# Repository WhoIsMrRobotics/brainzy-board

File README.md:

# Brainzy Board

Il s'agit d'une alternative aux cartes Arduino pour facilement construire son propre robot différentiel ou omnidirectionel. Basé sur une [Teensy 3.5](https://www.pjrc.com/store/teensy35.html), la Brainzy board se programme en C++ à travers l'[IDE Arduino](https://www.arduino.cc/en/Main/Software) à l'aide de la [bibliothèque Brainzy](https://github.com/WhoIsMrRobotics/brainzy-library). De nombreux modules peuvent être ajoutés à la carte pour étendre la complexité de vos créations.

Il existe deux types de modules :
* Les *Widgets*, dont la connection se fait par des connecteurs magnétiques et la communication via un bus I2C ;
* Les *extensions*, dont la connection se fait par des connecteurs standards et la communication via des bus SPI, UART, et/ou I2C.

Pour plus d'information, consultez notre site [www.mr-robotics.com](https://www.mr-robotics.com/).

**Caractéristiques de la Brainzy Board**

* *Mode d'utilisation :* 2 choix possibles pour le déplacement du robot : entrainement différenciel (2 roues) ou entrainement omnidirectionel (3 roues)
* *Dimensions de la carte :* 100mm x 100mm (forme hexagonale)
* *Moyens de communication :* USB, Bluetooth et Wifi

**Ports Entrées/Sorties**

* 1 port micro-USB
* 8 ports I2C, 3 ports SPI, 2 ports UART
* 3 ports pour des moteurs DC dotés de codeurs incrémentaux (deux channels)
* 1 lecteur de carte nano-SD
* 1 port pour vérifier l'état de charge de la batterie (jusqu'à 3 cellules)
* 1 Buzzer
* 1 interrupteur programmable
* 2 LEDs programmables

**Modules intégrés**

* 1 Module bluetooth (HC-05)
* 1 Module Wifi (ESP8266-01)

**Exemples de Widgets associés**

* IMU : accéléromètre 3 axes + gyroscope 3 axes (MPU-6050)
* Système d'éclairage : NeoPixels (WS2812B)
* Télémètre à ultrasons : Sonar (HC-SR04)
* Télémètre infrarouge : Sharp (GP2Y0A41SK0F)
* ...

**Exemples d'extensions associées**

* Bras poly-articulé
* Système de webcam pilotée
* Télécomande bluetooth
* Écran tactile
* ...

## Comment l'obtenir ?

Vous pouvez la commander en [nous contactant](mailto:bonjour@mr-robotics.com) ou suivre les étapes suivantes :
1. Réalisez le PCB à l'aide des fichiers GERBER.
2. Commandez les composants répertoriés dans le fichier BOM, puis soudez les.
3. Soudez une Teensy 3.5 en faisant attention aux indications suivantes.

## Quelques tutoriels

* Pour obtenir un modèle CAO de la carte, consultez [ce lien](https://www.youtube.com/watch?v=ekHAkWB-WTM).
* Pour générer les fichiers Gerber nécessaire à la production du PCB, consultez [ce lien](https://learn.sparkfun.com/tutorials/designing-pcbs-advanced-smd/gerber-generation).

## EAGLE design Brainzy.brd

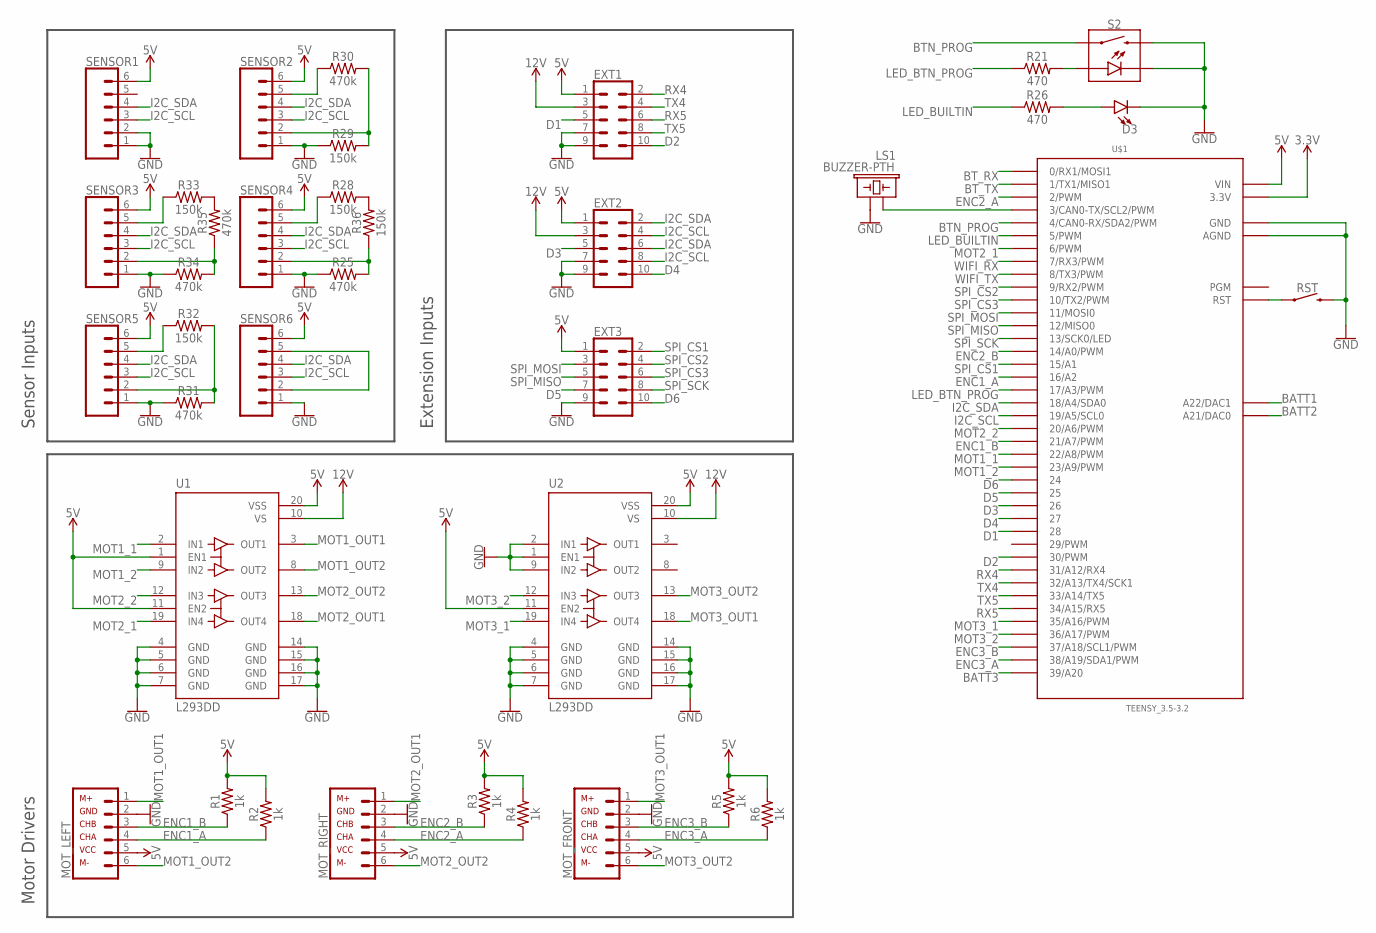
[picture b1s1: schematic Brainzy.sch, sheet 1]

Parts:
D3: LED-FKIT-1206; FKIT-LED-1206
EXT1, EXT2, EXT3: CONN_05X2SHD_LOCK; 2X5-SHROUDED_LOCK
LS1: BUZZER-PTH; BUZZER-12MM
MOT_FRONT: DC-MOTOR-CONNECTOR; JST-PH6
MOT_LEFT: DC-MOTOR-CONNECTOR; JST-PH6
MOT_RIGHT: DC-MOTOR-CONNECTOR; JST-PH6
R1, R2, R3, R4, R5, R6: 1k; 1206
R21, R26: 470; 1206
R25, R30, R31, R34, R35: 470k; 1206
R28, R29, R32, R33, R36: 150k; 1206
RST: MOMENTARY-SWITCH-SPST-PTH-6.0MM; TACTILE_SWITCH_PTH_6.0MM
S2: MOMENTARY-SWITCH-SPST-LED-PTH-12MM; TACTILE_SWITCH_LED_PTH_12MM
SENSOR1, SENSOR2, SENSOR3, SENSOR4, SENSOR5, SENSOR6: JST-ZH6
U1, U2: L293DD; SOIC127P1033X265-20N
U$1: TEENSY_3.5-3.2

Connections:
3.3V: U$1.3.3V, U$1.3.3V1 (3.3V), U$1.3.3V2 (3.3V), U$1.3.3V3 (3.3V); also elsewhere on the board
5V: EXT1.1, EXT2.1, EXT3.1, MOT_FRONT.5 (5-CHA), MOT_LEFT.5 (5-CHA), MOT_RIGHT.5 (5-CHA), R1.2, R2.2, R3.2, R4.2, R5.2, R6.2, SENSOR1.6, SENSOR2.6, SENSOR3.6, SENSOR4.6, SENSOR5.6, SENSOR6.6, U1.1 (EN1), U1.11 (EN2), U1.20 (VSS), U2.11 (EN2), U2.20 (VSS), U$1.VIN; also elsewhere on the board
12V: EXT1.3, EXT2.3, U1.10 (VS), U2.10 (VS); also elsewhere on the board
BATT1: U$1.A22 (A22/DAC1); also elsewhere on the board
BATT2: U$1.A21 (A21/DAC0); also elsewhere on the board
BATT3: U$1.39/A20; also elsewhere on the board
BTN_PROG: S2.4 (1), U$1.4 (4/CAN0-RX/SDA2/PWM)
BT_RX: U$1.0 (0/RX1/MOSI1); also elsewhere on the board
BT_TX: U$1.1 (1/TX1/MISO1); also elsewhere on the board
BUZZER: LS1.+ (1), U$1.3 (3/CAN0-TX/SCL2/PWM)
D1: EXT1.5, U$1.28
D2: EXT1.10, U$1.30 (30/PWM)
D3: EXT2.5, U$1.26
D4: EXT2.10, U$1.27
D5: EXT3.7, U$1.25
D6: EXT3.10, U$1.24
ENC1_A: MOT_LEFT.4 (4-GND), R2.1, U$1.16/A2
ENC1_B: MOT_LEFT.3 (3-VCC), R1.1, U$1.21/A7 (21/A7/PWM)
ENC2_A: MOT_RIGHT.4 (4-GND), R4.1, U$1.2 (2/PWM)
ENC2_B: MOT_RIGHT.3 (3-VCC), R3.1, U$1.14/A0 (14/A0/PWM)
ENC3_A: MOT_FRONT.4 (4-GND), R6.1, U$1.38/A19 (38/A19/SDA1/PWM)
ENC3_B: MOT_FRONT.3 (3-VCC), R5.1, U$1.37/A18 (37/A18/SCL1/PWM)
GND: D3.C, EXT1.7, EXT1.9, EXT2.7, EXT2.9, EXT3.9, LS1.- (2), MOT_FRONT.2 (2-M+), MOT_LEFT.2 (2-M+), MOT_RIGHT.2 (2-M+), R25.1, R29.1, R31.1, R34.1, RST.3 (2), S2.2, S2.C, SENSOR1.1, SENSOR1.2, SENSOR2.1, SENSOR3.1, SENSOR4.1, SENSOR5.1, SENSOR6.1, U1.4 (GND), U1.5 (GND), U1.6 (GND), U1.7 (GND), U1.14 (GND), U1.15 (GND), U1.16 (GND), U1.17 (GND), U2.1 (EN1), U2.2 (IN1), U2.4 (GND), U2.5 (GND), U2.6 (GND), U2.7 (GND), U2.9 (IN2), U2.14 (GND), U2.15 (GND), U2.16 (GND), U2.17 (GND), U$1.AGND, U$1.GND, U$1.GND1 (GND), U$1.GND2 (GND), U$1.GND3 (GND); also elsewhere on the board
I2C_SCL: EXT2.4, EXT2.8, SENSOR1.3, SENSOR2.3, SENSOR3.3, SENSOR4.3, SENSOR5.3, SENSOR6.3, U$1.19/A5 (19/A5/SCL0)
I2C_SDA: EXT2.2, EXT2.6, SENSOR1.4, SENSOR2.4, SENSOR3.4, SENSOR4.4, SENSOR5.4, SENSOR6.4, U$1.18/A4 (18/A4/SDA0)
LED_BTN_PROG: R21.1, U$1.17/A3 (17/A3/PWM)
LED_BUILTIN: R26.1, U$1.5 (5/PWM)
MOT1_1: U1.2 (IN1), U$1.22/A8 (22/A8/PWM)
MOT1_2: U1.9 (IN2), U$1.23/A9 (23/A9/PWM)
MOT1_OUT1: MOT_LEFT.1 (1-M-), U1.3 (OUT1)
MOT1_OUT2: MOT_LEFT.6 (6-CHB), U1.8 (OUT2)
MOT2_1: U1.19 (IN4), U$1.6 (6/PWM)
MOT2_2: U1.12 (IN3), U$1.20/A6 (20/A6/PWM)
MOT2_OUT1: MOT_RIGHT.1 (1-M-), U1.18 (OUT4)
MOT2_OUT2: MOT_RIGHT.6 (6-CHB), U1.13 (OUT3)
MOT3_1: U2.19 (IN4), U$1.35/A16 (35/A16/PWM)
MOT3_2: U2.12 (IN3), U$1.36/A17 (36/A17/PWM)
MOT3_OUT1: MOT_FRONT.1 (1-M-), U2.18 (OUT4)
MOT3_OUT2: MOT_FRONT.6 (6-CHB), U2.13 (OUT3)
unnamed: D3.A, R26.2
unnamed: R21.2, S2.A
unnamed: SENSOR6.2, SENSOR6.5
unnamed: R25.2, R36.1, SENSOR4.2
unnamed: R28.1, SENSOR4.5
unnamed: R31.2, R32.2, SENSOR5.2
unnamed: R32.1, SENSOR5.5
unnamed: R29.2, R30.2, SENSOR2.2
unnamed: R30.1, SENSOR2.5
unnamed: R33.2, R35.2
unnamed: R34.2, R35.1, SENSOR3.2
unnamed: R33.1, SENSOR3.5
unnamed: R28.2, R36.2
RST: RST.1, U$1.RST_3.5 (RST)
RX4: EXT1.2, U$1.31/A12 (31/A12/RX4)
RX5: EXT1.6, U$1.34/A15 (34/A15/RX5)
SPI_CS1: EXT3.2, U$1.15/A1
SPI_CS2: EXT3.4, U$1.9 (9/RX2/PWM)
SPI_CS3: EXT3.6, U$1.10 (10/TX2/PWM)
SPI_MISO: EXT3.5, U$1.12 (12/MISO0)
SPI_MOSI: EXT3.3, U$1.11 (11/MOSI0)
SPI_SCK: EXT3.8, U$1.13 (13/SCK0/LED)
TX4: EXT1.4, U$1.32/A13 (32/A13/TX4/SCK1)
TX5: EXT1.8, U$1.33/A14 (33/A14/TX5)
WIFI_RX: U$1.7 (7/RX3/PWM); also elsewhere on the board
WIFI_TX: U$1.8 (8/TX3/PWM); also elsewhere on the board

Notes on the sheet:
Motor Drivers
Sensor Inputs
Extension Inputs

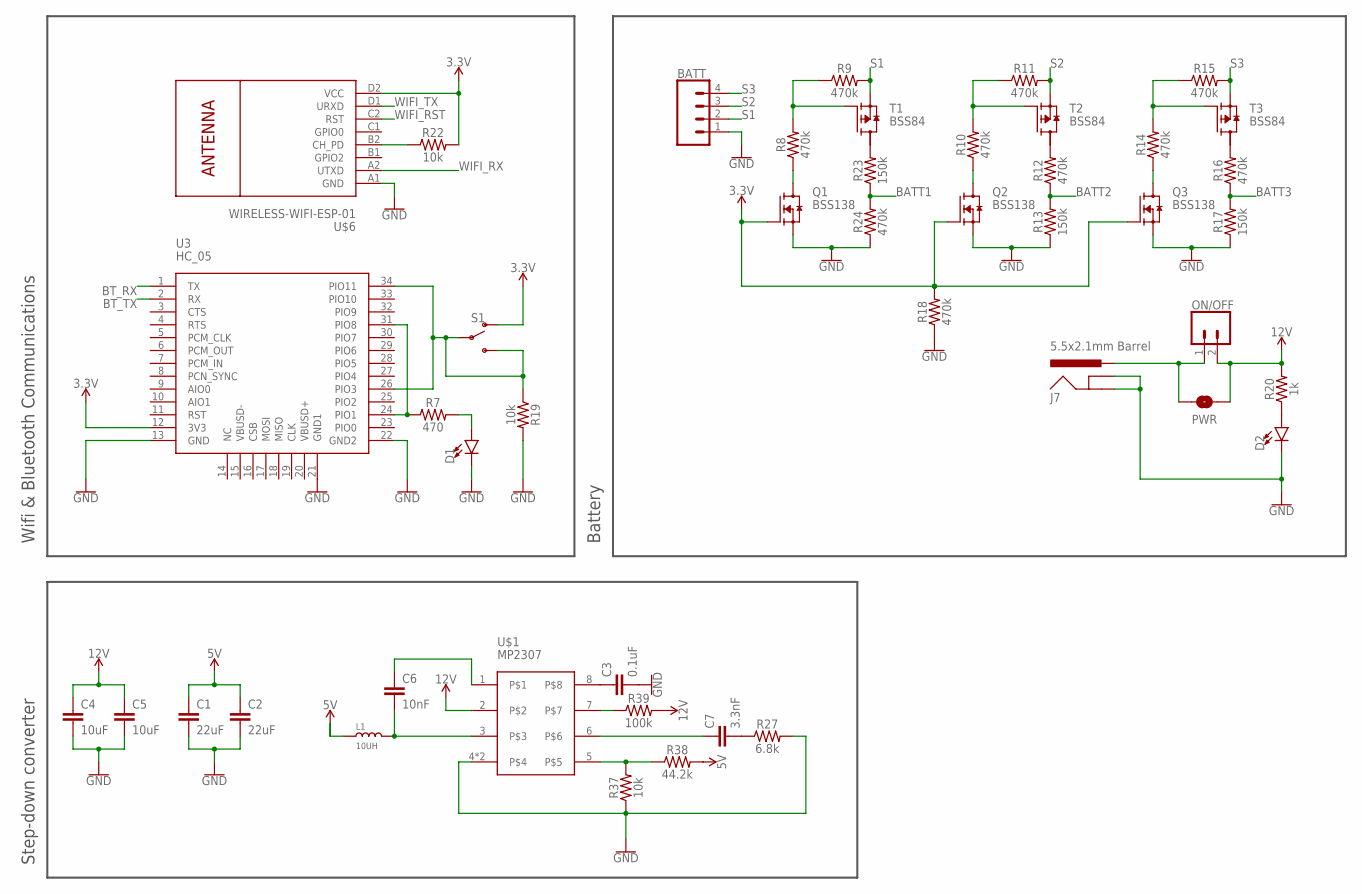
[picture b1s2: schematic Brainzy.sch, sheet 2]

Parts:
BATT: CONN_04LOCK_LONGPADS; 1X04_LOCK_LONGPADS
BK: MP2307; SOIC127P600X170-9N
C1, C2: 22uF; 0805
C3: 0.1uF; 0603
C4, C5: 10uF; 1210
C6: 10nF; 0603
C7: 3.3nF; 0603
D1, D2: LED-FKIT-1206; FKIT-LED-1206
J7: 5.5x2.1mm Barrel; POWER_JACK_SMD
L1: 10UH; SMD-2P-L6.0XW6.0XH3.0MM
ON/OFF: JST-XH-02-PIN-LONG-PAD; JST-XH-02-PACKAGE-LONG-PAD
PWR: JUMPER-SMT_2_NO_SILK; SMT-JUMPER_2_NO_SILK
Q1, Q2, Q3: BSS138; SOT23
R7: 470; 1206
R8, R9, R10, R11, R12, R14, R15, R16, R18, R24: 470k; 1206
R13, R17, R23: 150k; 1206
R19, R22: 10k; 1206
R20: 1k; 1206
R27: 6.8k; 0603
R37: 10k; 0603
R38: 44.2k; 0603
R39: 100k; 0603
S1: SWITCH-SPDT-SMD-RIGHT-ANGLE; SWITCH_SPST_SMD_A
T1, T2, T3: BSS84; SOT23
U3: HC_05; BLUETOOTH_SMD
U$6: WIRELESS-WIFI-ESP-01

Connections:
3.3V: Q1.1 (G), Q2.1 (G), Q3.1 (G), R18.2, R22.2, S1.1 (O), U3.12 (3V3), U$6.D2 (VCC); also elsewhere on the board
5V: C1.1, C2.1, L1.1, R38.2; also elsewhere on the board
12V: BK.2, C4.1, C5.1, ON/OFF.2, PWR.2, R20.2, R39.2; also elsewhere on the board
BATT1: R23.1, R24.2; also elsewhere on the board
BATT2: R12.1, R13.2; also elsewhere on the board
BATT3: R16.1, R17.2; also elsewhere on the board
BT_RX: U3.1 (TX); also elsewhere on the board
BT_TX: U3.2 (RX); also elsewhere on the board
GND: BATT.1, BK.4, BK.9, C1.2, C2.2, C3.2, C4.2, C5.2, D1.C, D2.C, J7.GND (GNDBREAK), J7.P$4 (GND), Q1.2 (S), Q2.2 (S), Q3.2 (S), R13.1, R17.1, R18.1, R19.2, R24.1, R27.2, R37.1, U3.13 (GND), U3.21 (GND1), U3.22 (GND2), U$6.A1 (GND); also elsewhere on the board
unnamed: R12.2, T2.3 (D)
unnamed: D2.A, R20.1
unnamed: R22.1, U$6.B2 (CH_PD)
unnamed: R8.2, R9.1, T1.1 (G)
unnamed: Q1.3 (D), R8.1
unnamed: R16.2, T3.3 (D)
unnamed: R10.2, R11.1, T2.1 (G)
unnamed: BK.7, R39.1
unnamed: R7.1, U3.24 (PIO1), U3.31 (PIO8)
unnamed: D1.A, R7.2
unnamed: Q2.3 (D), R10.1
unnamed: R14.2, R15.1, T3.1 (G)
unnamed: Q3.3 (D), R14.1
unnamed: J7.VIN0 (PWR), ON/OFF.1, PWR.1
unnamed: R19.1, S1.2, S1.3 (S), U3.26 (PIO3), U3.34 (PIO11)
unnamed: R23.2, T1.3 (D)
unnamed: BK.5, R37.2, R38.1
unnamed: BK.8, C3.1
unnamed: BK.6, C7.1
unnamed: BK.3, C6.2, L1.2
unnamed: C7.2, R27.1
unnamed: BK.1, C6.1
S1: BATT.2, R9.2, T1.2 (S)
S2: BATT.3, R11.2, T2.2 (S)
S3: BATT.4, R15.2, T3.2 (S)
WIFI_RST: U$6.C2 (RST)
WIFI_RX: U$6.A2 (UTXD); also elsewhere on the board
WIFI_TX: U$6.D1 (URXD); also elsewhere on the board

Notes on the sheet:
Wifi & Bluetooth Communications
Battery
Step-down converter

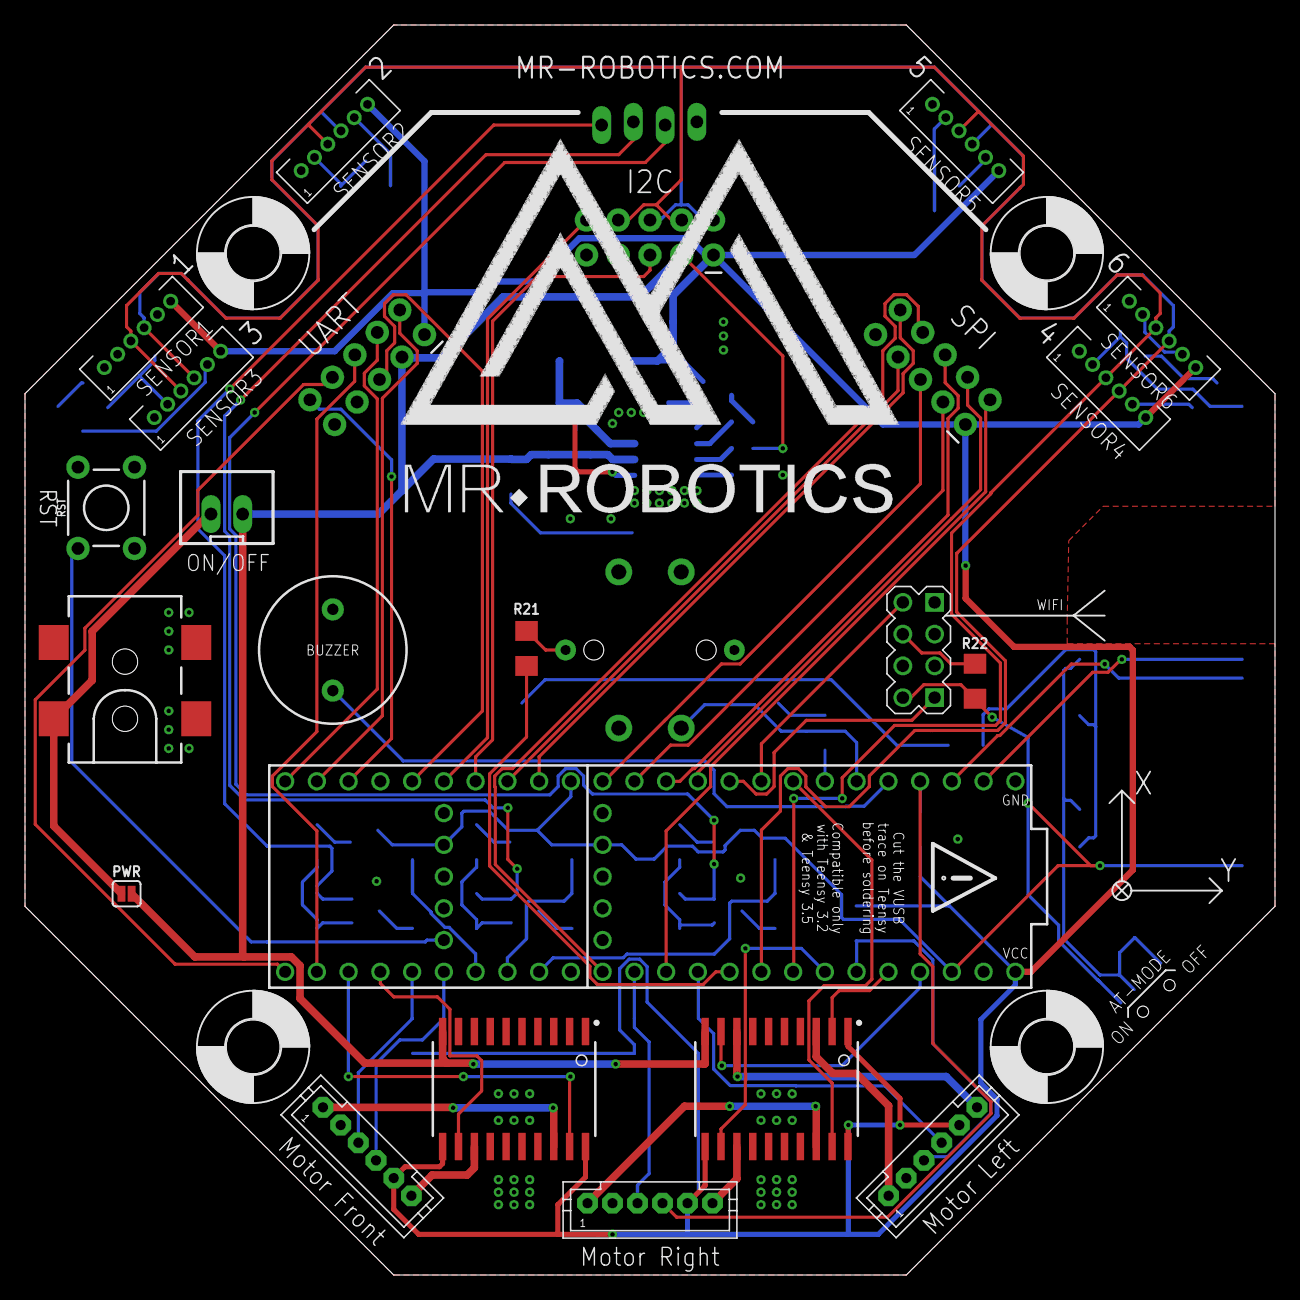
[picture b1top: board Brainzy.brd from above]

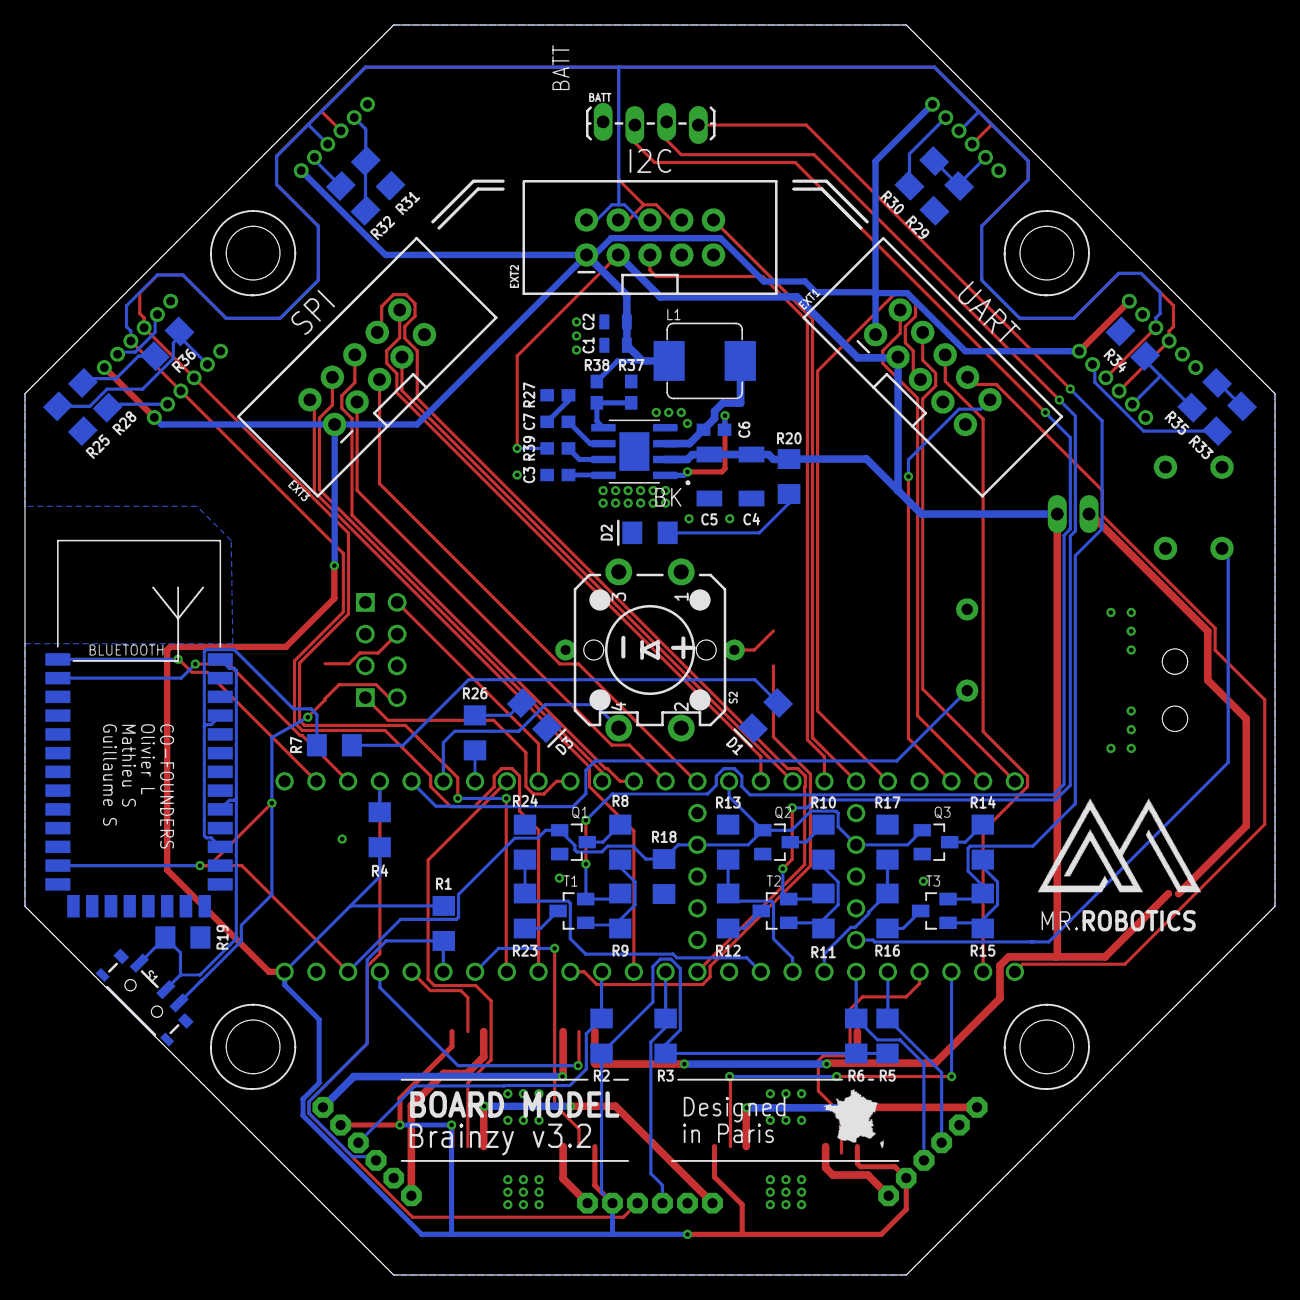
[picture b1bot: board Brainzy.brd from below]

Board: 2 copper layers, 100.0 x 100.0 mm, 90 parts (64 on the bottom side), 90 nets.

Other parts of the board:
U$3: LOGO_FR
U$4: M_40MM
U$8, U$9, U$10, U$11: 4,3
U$12: LOGO_M
U$13: NAME_40MM

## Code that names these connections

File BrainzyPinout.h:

/************************************************************************
 * File : config.h                                                      *
 *  Configuration file for Kbots main shield.                           *
 *                                                                      *
 ************************************************************************/

#ifndef __CONFIG_ROBOT_H
#define __CONFIG_ROBOT_H

/* ---------------- 
  Teensy 3.2
---------------- */

//Motors Drivers
#define MOT1_1 23
#define MOT1_2 22
#define COD1_A 15
#define COD1_B  14

#define MOT2_1 21
#define MOT2_2 20
#define COD2_A 17
#define COD2_B 16

//UART
#define USB Serial
#define Bluetooth Serial1

//SPI
#define SPI_MOSI 11
#define SPI_MISO 12
#define SPI_SCK 13
#define SPI_CS1 8
#define SPI_CS2 9
#define SPI_CS3 10

//I2C
#define I2C_SDA 18
#define I2C_SCL 19

//User Interface
#define UI_BTN_DOWN 6
#define UI_BTN_LEFT 3
#define UI_BTN_CENTER 4
#define UI_BTN_RIGHT 5
#define UI_BTN_UP 2

#define BUZZER 7

/* ---------------- 
  Teensy 3.5
---------------- */

//Motor Driver
#define MOT3_1 30
#define MOT3_2 29
#define COD3_A 28
#define COD3_B 27

//Power Monitoring
#define CELL1 A22
#define CELL2 A21
#define CELL3 A20 

//IR Range Sensors
#define SHARP1 A14
#define SHARP2 A15
#define SHARP3 A16
#define SHARP4 A17
#define SHARP5 A13
#define SHARP6 A12

//Radio Comunications
#define RF_CE 37
#define RF_CS 38

//Extensions for touch screen
#define T_IRQ 24
#define T_CS1 25
#define T_CS2 26

#endif

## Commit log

2018-09-30 Upload Brainzy v1.0
2018-09-30 Upload Brainzy v1.1
2018-09-30 Upload Brainzy v2.0
2018-09-30 Upload Brainzy v2.1
2018-09-30 Upload Brainzy v3.0
2018-09-30 Upload Brainzy v3.1
2018-09-30 Upload Brainzy v3.2
2018-09-30 Upload Brainzy v3.2.1
2018-11-30 Add BOM file
2018-11-30 Add some pictures

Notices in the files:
parts and their libraries:
SparkFun-Connectors: Licensing: Creative Commons ShareAlike 4.0 International - https://creativecommons.org/licenses/by-sa/4.0
